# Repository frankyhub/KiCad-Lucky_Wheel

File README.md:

<div align="center">

|[:skull:ISSUE](https://github.com/frankyhub/KiCad-Lucky_Wheel/issues?q=is%3Aissue)|[:speech_balloon: Forum /Discussion](https://github.com/frankyhub/KiCad-Lucky_Wheel/discussions)|[:grey_question:WiKi](https://github.com/frankyhub/KiCad-Lucky_Wheel/wiki)||
|--|--|--|--|
| | | | |
<a href="https://github.com/frankyhub/KiCad-Lucky_Wheel/issues">|<a href="https://github.com/frankyhub/KiCad-Lucky_Wheel/discussions">|<a href="https://github.com/frankyhub/KiCad-Lucky_Wheel/6eleases">||
|| <a href="https://github.com/frankyhub/KiCad-Lucky_Wheel/pulse" alt="Activity">| <a href="https://github.com/frankyhub/KiCad-Lucky_Wheel/graphs/traffic">  |<a href="https://github.com/frankyhub?tab=stars"> ||

<br> <br>

</div>

## Story
Mit einem Tastendruck starten wir den immer langsam werdenden LED-Umlauf. Irgendwann stoppt der LED-Umlauf und zeigt dir deine Glückszahl. Hast du richtig getippt?

### BOM

| Anzahl | Bezeichnung | 
| -------- | -------- | 
| 1  |  NE555  |
|  1 |  CD4017  |
|  1 |  BC548  |
|  10 |  LED rt  |
| 1  |  1uF  |
| 1  |  47uF |
| 1  |  1,2k  |
|  1 |  10k  |
|  2 |  470k  |
|  1 |  Taster  |
|  1 |  Batterieklipp  | 
|  1 |   9V Batterie | 
|  1 |  Platine | 
|  --- |  --- | 

---

<div style="position:absolute; left:2cm; ">   
<ol class="breadcrumb" style="border-top: 2px solid black;border-bottom:2px solid black; height: 45px; width: 900px;"> <p align="center"><a href="#oben">nach oben</a></p></ol>
</div>  

---

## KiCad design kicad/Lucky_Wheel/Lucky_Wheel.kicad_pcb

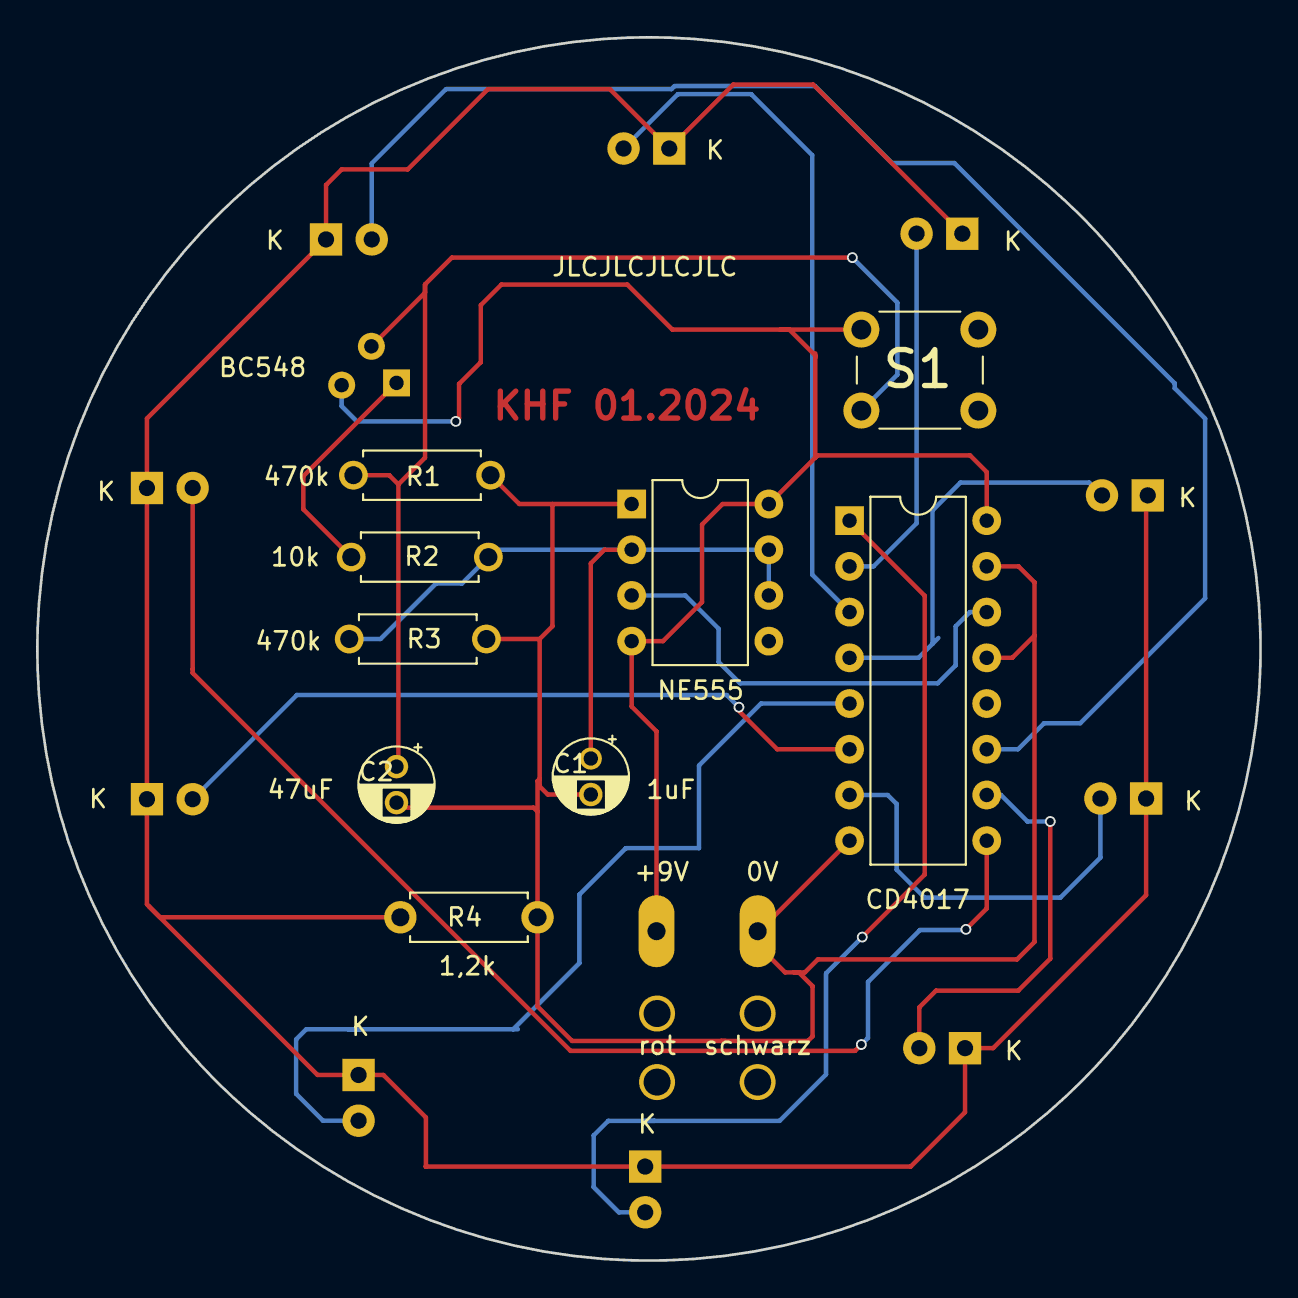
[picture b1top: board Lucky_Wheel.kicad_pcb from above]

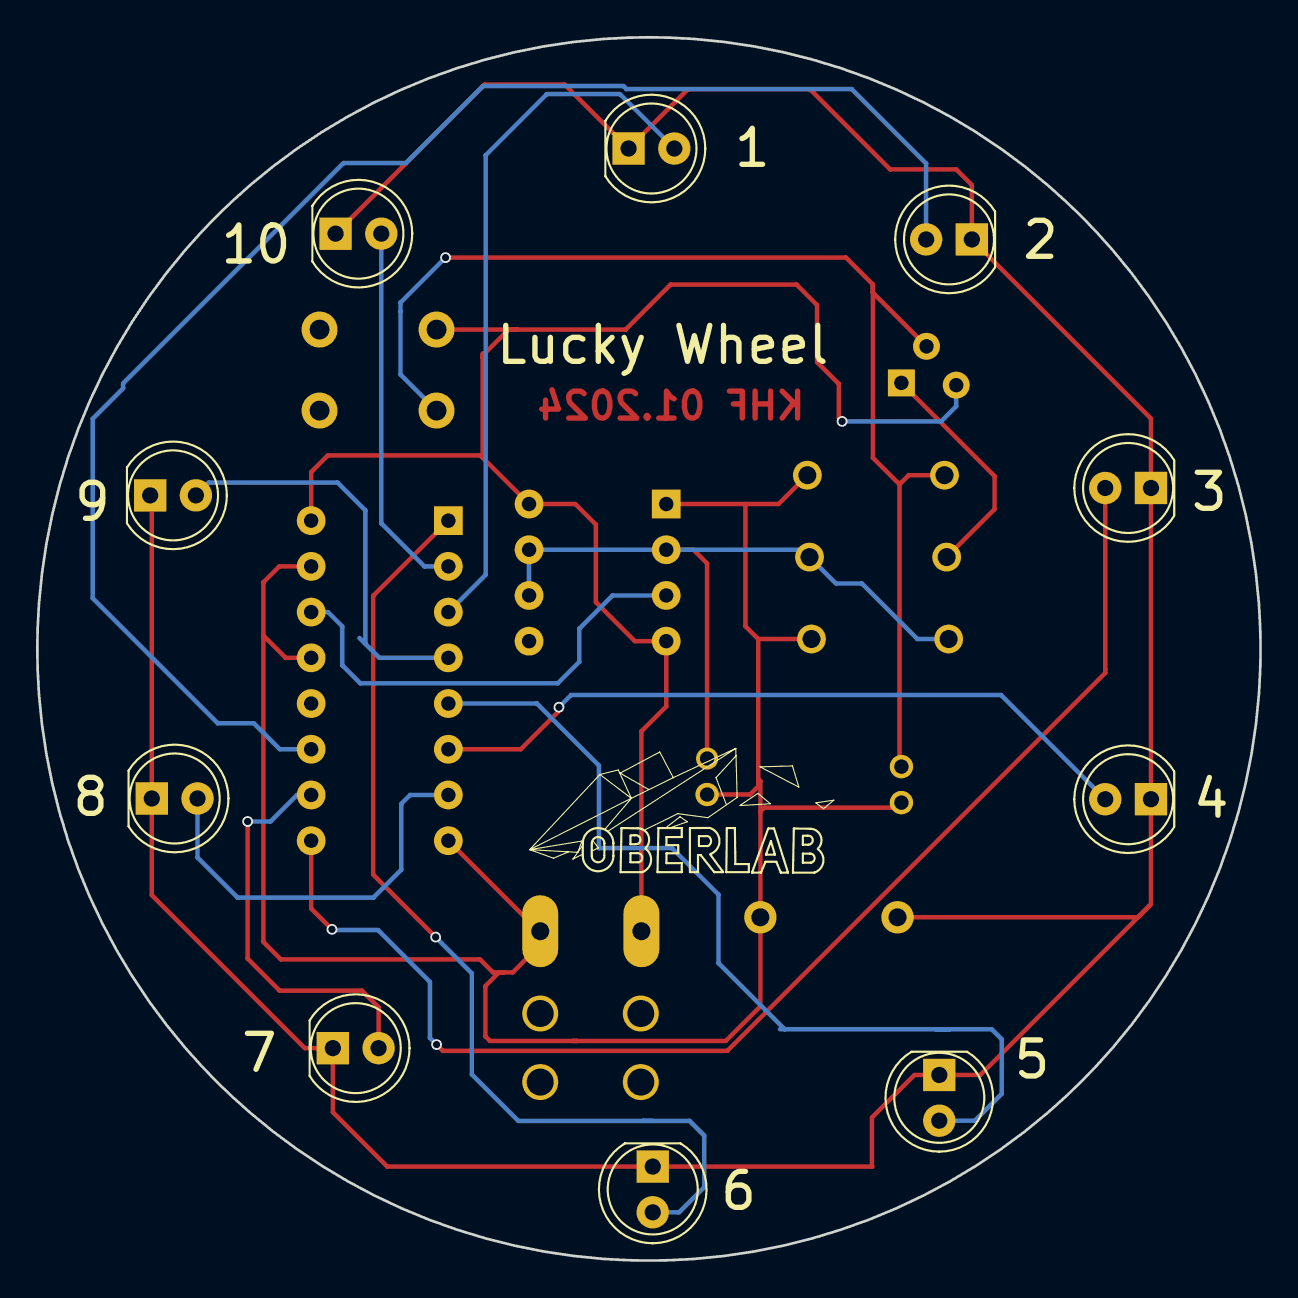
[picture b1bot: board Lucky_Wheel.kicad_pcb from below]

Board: 2 copper layers, 68.0 x 68.0 mm, 25 parts (10 on the bottom side), 16 nets.

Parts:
0V: LP_GND; LP
1, 2, 3, 4, 5, 6, 7, 8, 9, 10: LED; LED_D5.0mm
+9V: LP
C1: 1uF; CP_Radial_D4.0mm_P2.00mm
C2: 47uF; CP_Radial_D4.0mm_P2.00mm
LP: LP
LP#2, LP#3, LP#4: LP
R1, R3: 470k; R_Axial_DIN0207_L6.3mm_D2.5mm_P7.62mm_Horizontal
R2: 10k; R_Axial_DIN0207_L6.3mm_D2.5mm_P7.62mm_Horizontal
R4: 1,2k; R_Axial_DIN0207_L6.3mm_D2.5mm_P7.62mm_Horizontal
S1: SW_PUSH_6mm_H5mm
U2: NE555; DIP-8_W7.62mm
U3: CD4017; DIP-16_W7.62mm

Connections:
unnamed: C1.1, R2.2, R3.1, U2.2, U2.6, U2.7
unnamed: 0V.1, C1.2, C2.2, R1.2, R3.2, R4.2, U2.1, U3.8, U3.13, U3.15
unnamed: C2.1, R1.1, S1.2
unnamed: 1.2, U3.3
unnamed: 2.2, U3.2
unnamed: 3.2, U3.4
unnamed: 4.2, U3.7
unnamed: 5.2, U3.10
unnamed: 6.2, U3.1
unnamed: 7.2, U3.5
unnamed: 8.2, U3.6
unnamed: 9.2, U3.9
unnamed: 1.1, 2.1, 3.1, 4.1, 5.1, 6.1, 7.1, 8.1, 9.1, 10.1, R4.1
unnamed: 10.2, U3.11
unnamed: +9V.1, S1.1, U2.4, U2.8, U3.16
unnamed: U2.3, U3.14

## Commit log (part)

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2024-02-28 V 1.2024
2024-03-05 BOM Update README.md
2024-04-02 V1.0 02.04.2024
2024-04-02 V1.1 02.04.2024
2024-04-02 V1.2 02.04.2024
2024-08-08 V 08082024
2024-10-12 V12102024
